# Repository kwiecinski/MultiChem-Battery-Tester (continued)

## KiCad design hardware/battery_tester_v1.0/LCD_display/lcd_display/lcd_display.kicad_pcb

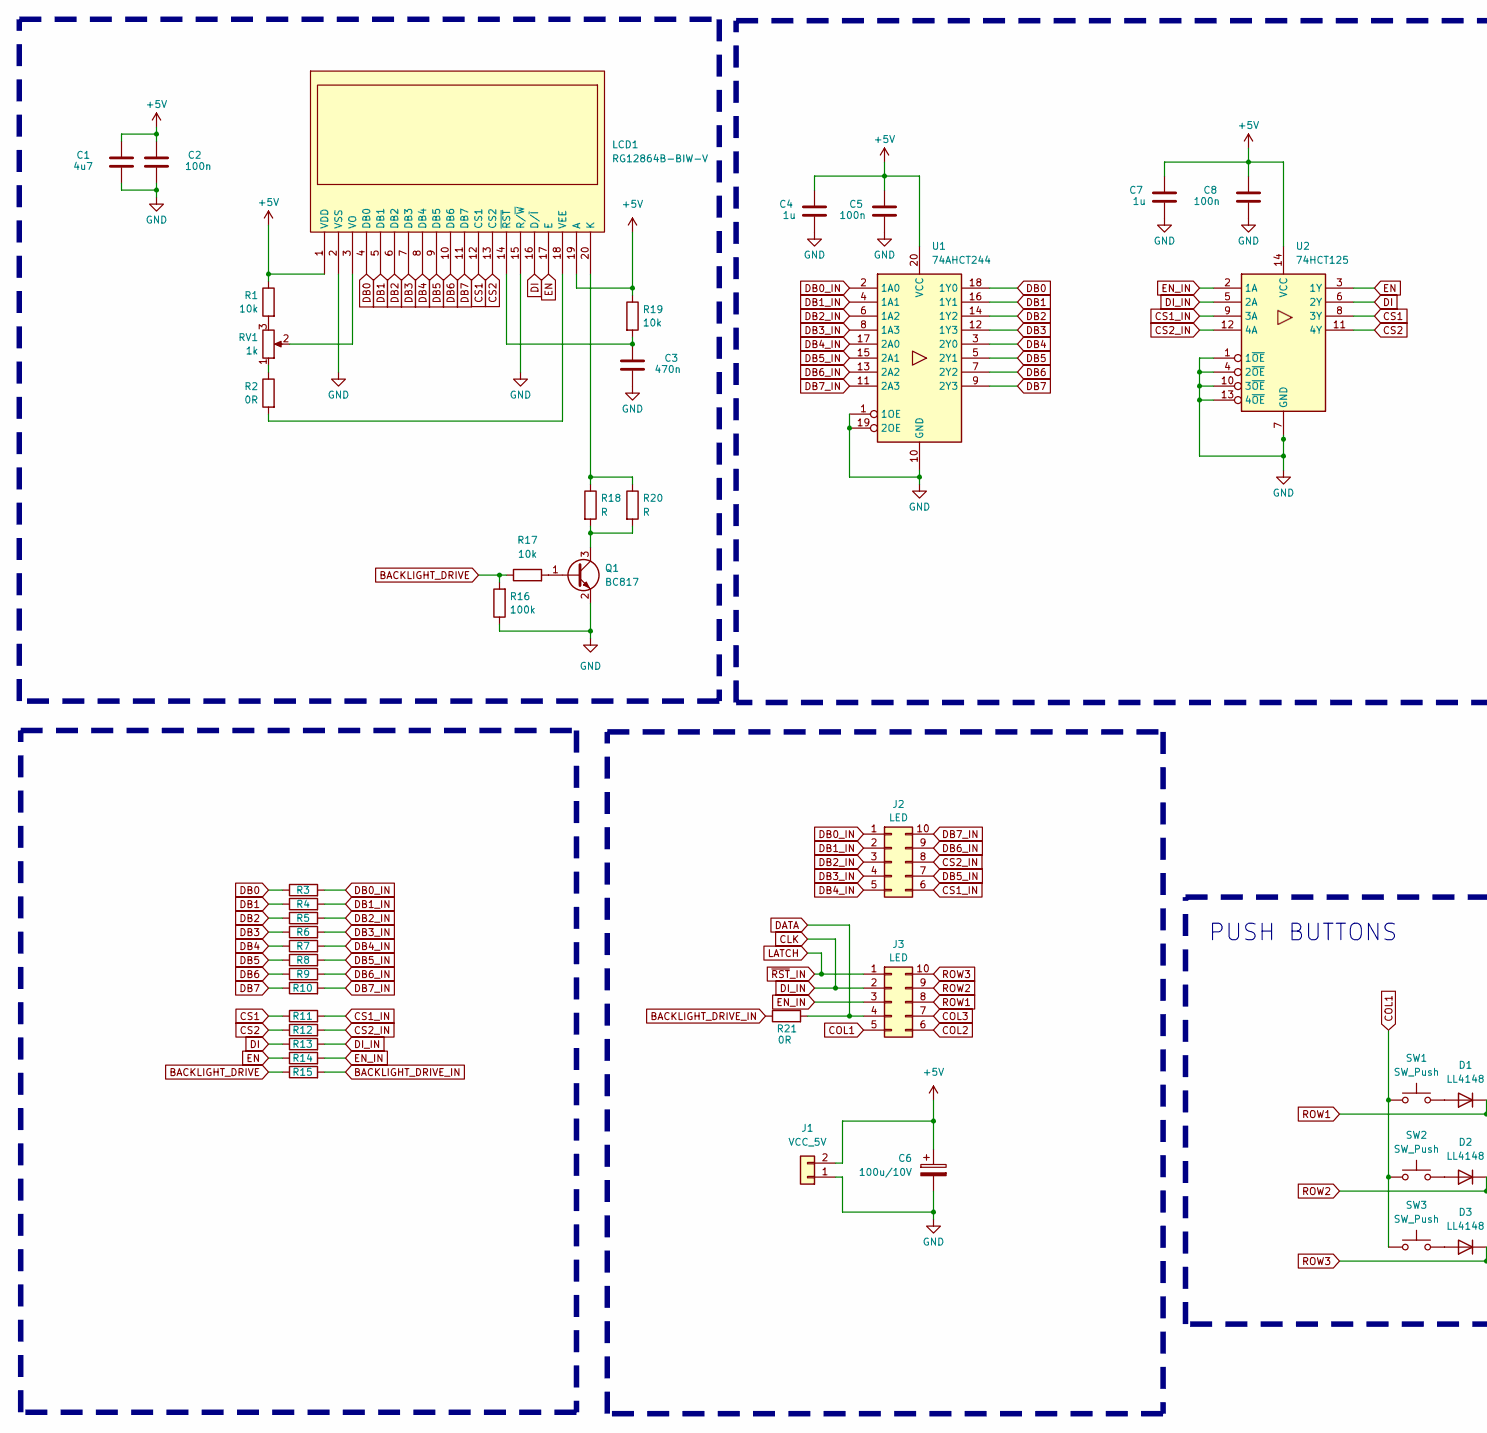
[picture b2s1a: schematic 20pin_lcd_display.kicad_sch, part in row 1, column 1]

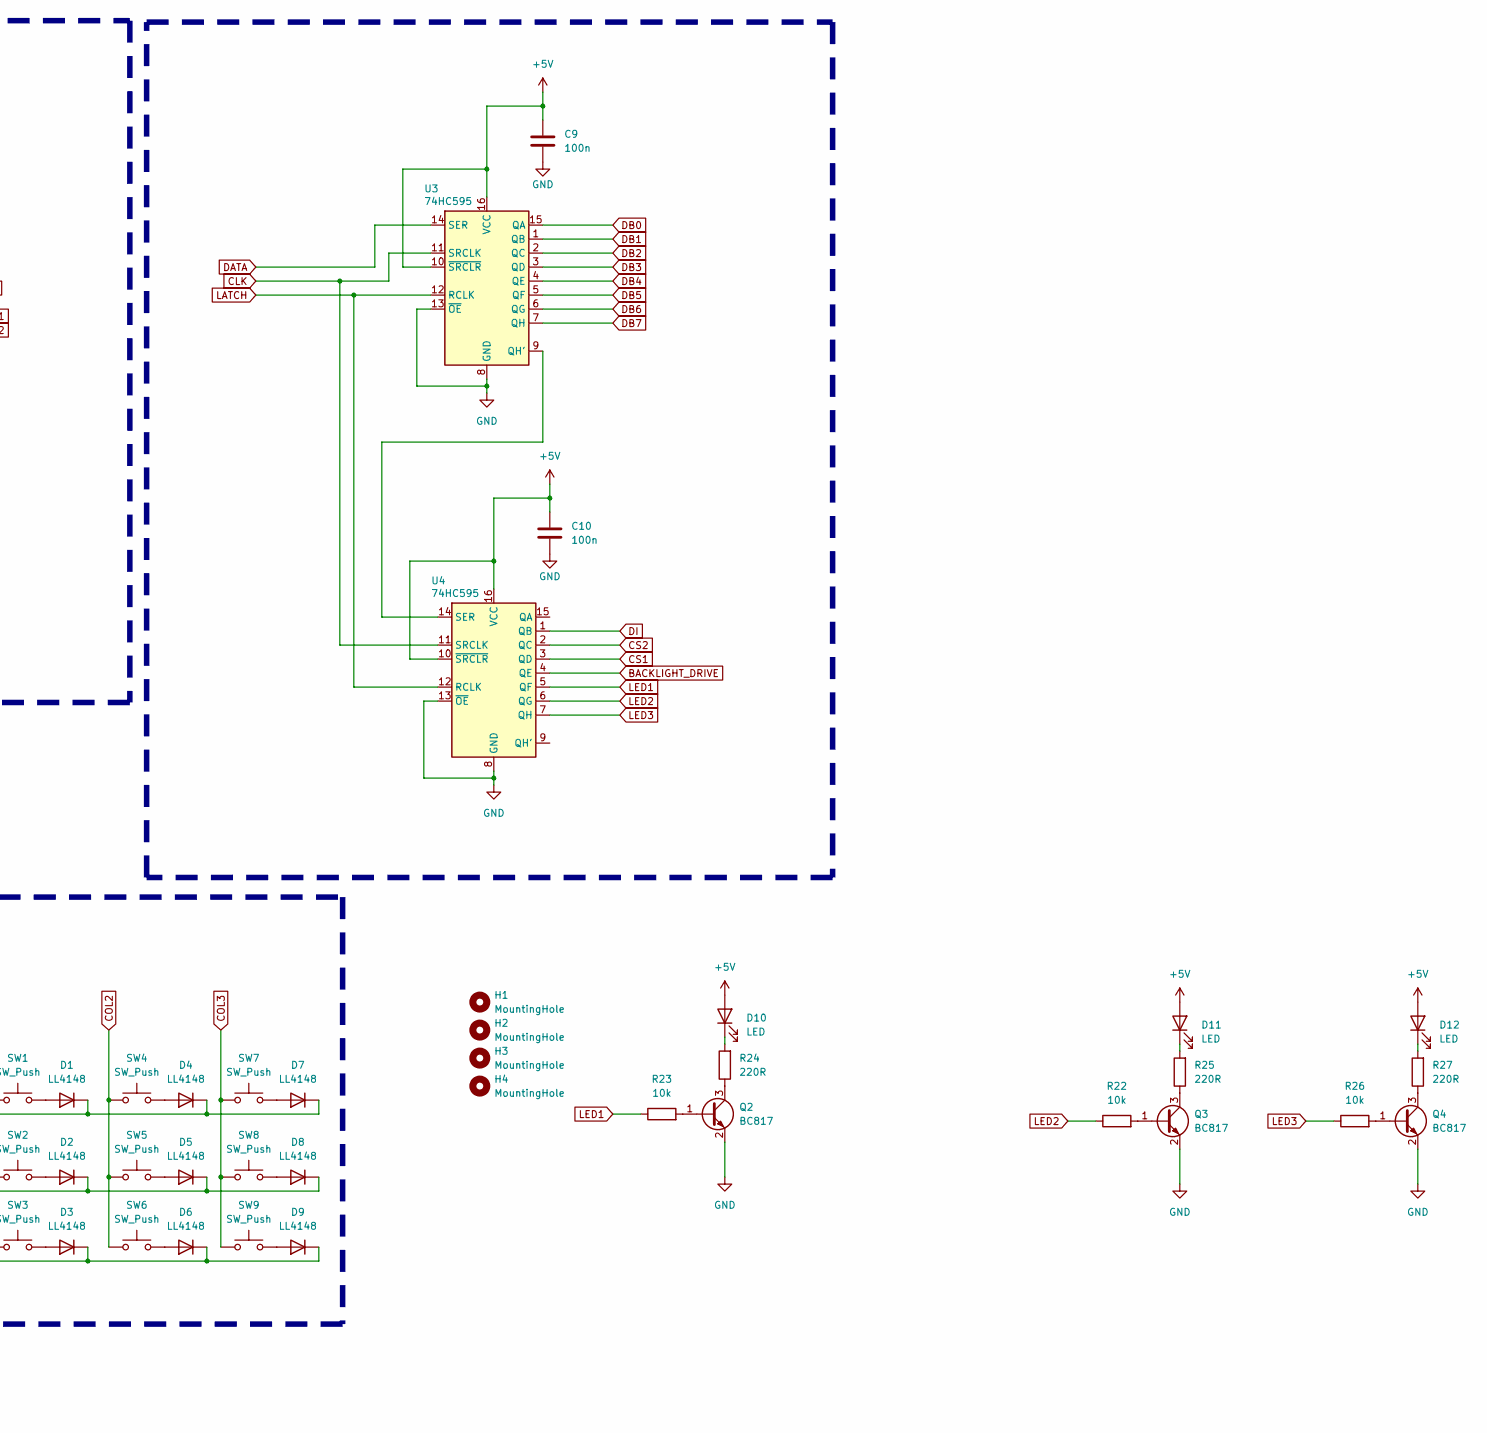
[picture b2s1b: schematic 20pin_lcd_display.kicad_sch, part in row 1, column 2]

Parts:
C1: 4u7; C_0805_2012Metric_Pad1.18x1.45mm_HandSolder
C2, C5, C8: 100n; C_0805_2012Metric_Pad1.18x1.45mm_HandSolder
C3: 470n; C_0805_2012Metric_Pad1.18x1.45mm_HandSolder
C4, C7: 1u; C_0805_2012Metric_Pad1.18x1.45mm_HandSolder
C6: 100u/10V; CP_Radial_D8.0mm_P3.80mm
C9, C10: 100n; C_0805_2012Metric
D1, D2, D3, D4, D5, D6, D7, D8, D9: LL4148; D_MiniMELF
D10, D11, D12: LED; LED_D5.0mm
H1, H2, H3, H4: MountingHole; Mount-Hole-3mm
J1: VCC_5V; JST_XA_B02B-XASK-1_1x02_P2.50mm_Vertical
J2, J3: LED; IDC-Header_2x05_P2.54mm_Vertical
LCD1: RG12864B-BIW-V; RG12864B_FULL
Q1, Q2, Q3, Q4: BC817; SOT-23
R1, R17, R19, R22, R23, R26: 10k; R_0805_2012Metric_Pad1.20x1.40mm_HandSolder
R2, R3, R4, R5, R6, R7, R8, R9, R10, R11, R12, R13, R14, R15, R21: 0R; R_0805_2012Metric_Pad1.20x1.40mm_HandSolder
R16: 100k; R_0805_2012Metric_Pad1.20x1.40mm_HandSolder
R18, R20: R; R_1206_3216Metric
R24, R25, R27: 220R; R_0805_2012Metric_Pad1.20x1.40mm_HandSolder
RV1: 1k; Potentiometer_ACP_CA9-V10_Vertical_Hole
SW1, SW2, SW3, SW4, SW5, SW6, SW7, SW8, SW9: SW_Push; SW_PUSH_6mm
U1: 74AHCT244; SOIC-20W_7.5x12.8mm_P1.27mm
U2: 74HCT125; SO-14_3.9x8.65mm_P1.27mm
U3, U4: 74HC595; SOIC-16_3.9x9.9mm_P1.27mm

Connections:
+5V: C1.1, C2.1, C4.1, C5.1, C6.1, C7.1, C8.1, C9.1, C10.1, D10.2 (A), D11.2 (A), D12.2 (A), J1.2, LCD1.1 (VDD), LCD1.19 (A), R1.1, R19.1, U1.20 (VCC), U2.14 (VCC), U3.10 (~SRCLR), U3.16 (VCC), U4.10 (~SRCLR), U4.16 (VCC)
BACKLIGHT_DRIVE: R15.1, R16.2, R17.1, U4.4 (QE)
BACKLIGHT_DRIVE_IN: R15.2, R21.1
CLK: J3.2, R13.2, U2.5 (2A), U3.11 (SRCLK), U4.11 (SRCLK)
COL1: J3.5, SW1.1, SW2.1, SW3.1
COL2: J3.6, SW4.1, SW5.1, SW6.1
COL3: J3.7, SW7.1, SW8.1, SW9.1
CS1: LCD1.12 (CS1), R11.1, U2.8 (3Y), U4.3 (QD)
CS1_IN: J2.6, R11.2, U2.9 (3A)
CS2: LCD1.13 (CS2), R12.1, U2.11 (4Y), U4.2 (QC)
CS2_IN: J2.8, R12.2, U2.12 (4A)
DATA: J3.4, R21.2, U3.14 (SER)
DB0: LCD1.4 (DB0), R3.1, U1.18 (1Y0), U3.15 (QA)
DB0_IN: J2.1, R3.2, U1.2 (1A0)
DB1: LCD1.5 (DB1), R4.1, U1.16 (1Y1), U3.1 (QB)
DB1_IN: J2.2, R4.2, U1.4 (1A1)
DB2: LCD1.6 (DB2), R5.1, U1.14 (1Y2), U3.2 (QC)
DB2_IN: J2.3, R5.2, U1.6 (1A2)
DB3: LCD1.7 (DB3), R6.1, U1.12 (1Y3), U3.3 (QD)
DB3_IN: J2.4, R6.2, U1.8 (1A3)
DB4: LCD1.8 (DB4), R7.1, U1.3 (2Y0), U3.4 (QE)
DB4_IN: J2.5, R7.2, U1.17 (2A0)
DB5: LCD1.9 (DB5), R8.1, U1.5 (2Y1), U3.5 (QF)
DB5_IN: J2.7, R8.2, U1.15 (2A1)
DB6: LCD1.10 (DB6), R9.1, U1.7 (2Y2), U3.6 (QG)
DB6_IN: J2.9, R9.2, U1.13 (2A2)
DB7: LCD1.11 (DB7), R10.1, U1.9 (2Y3), U3.7 (QH)
DB7_IN: J2.10, R10.2, U1.11 (2A3)
DI: LCD1.16 (D/~I), R13.1, U2.6 (2Y), U4.1 (QB)
EN: LCD1.17 (E), R14.1, U2.3 (1Y)
EN_IN: J3.3, R14.2, U2.2 (1A)
GND: C1.2, C2.2, C3.2, C4.2, C5.2, C6.2, C7.2, C8.2, C9.2, C10.2, J1.1, LCD1.2 (VSS), LCD1.15 (R/~W), Q1.2 (E), Q2.2 (E), Q3.2 (E), Q4.2 (E), R16.1, U1.1 (1OE), U1.10 (GND), U1.19 (2OE), U2.1 (1~OE), U2.4 (2~OE), U2.7 (GND), U2.10 (3~OE), U2.13 (4~OE), U3.8 (GND), U3.13 (~OE), U4.8 (GND), U4.13 (~OE)
LATCH: J3.1, U3.12 (RCLK), U4.12 (RCLK)
LED1: R23.1, U4.5 (QF)
LED2: R22.1, U4.6 (QG)
LED3: R26.1, U4.7 (QH)
unnamed: D1.2 (A), SW1.2
unnamed: D2.2 (A), SW2.2
unnamed: D3.2 (A), SW3.2
unnamed: D4.2 (A), SW4.2
unnamed: D5.2 (A), SW5.2
unnamed: D6.2 (A), SW6.2
unnamed: D7.2 (A), SW7.2
unnamed: D8.2 (A), SW8.2
unnamed: D9.2 (A), SW9.2
unnamed: D10.1 (K), R24.2
unnamed: D11.1 (K), R25.2
unnamed: D12.1 (K), R27.2
unnamed: LCD1.20 (K), R18.1, R20.1
unnamed: LCD1.18 (VEE), R2.2
unnamed: LCD1.3 (VO), RV1.2
unnamed: C3.1, LCD1.14 (~RST), R19.2
unnamed: Q1.1 (B), R17.2
unnamed: Q1.3 (C), R18.2, R20.2
unnamed: Q2.1 (B), R23.2
unnamed: Q2.3 (C), R24.1
unnamed: Q3.1 (B), R22.2
unnamed: Q3.3 (C), R25.1
unnamed: Q4.1 (B), R26.2
unnamed: Q4.3 (C), R27.1
unnamed: R1.2, RV1.3
unnamed: R2.1, RV1.1
unnamed: U3.9 (QH'), U4.14 (SER)
ROW1: D1.1 (K), D4.1 (K), D7.1 (K), J3.8
ROW2: D2.1 (K), D5.1 (K), D8.1 (K), J3.9
ROW3: D3.1 (K), D6.1 (K), D9.1 (K), J3.10

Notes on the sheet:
PUSH BUTTONS

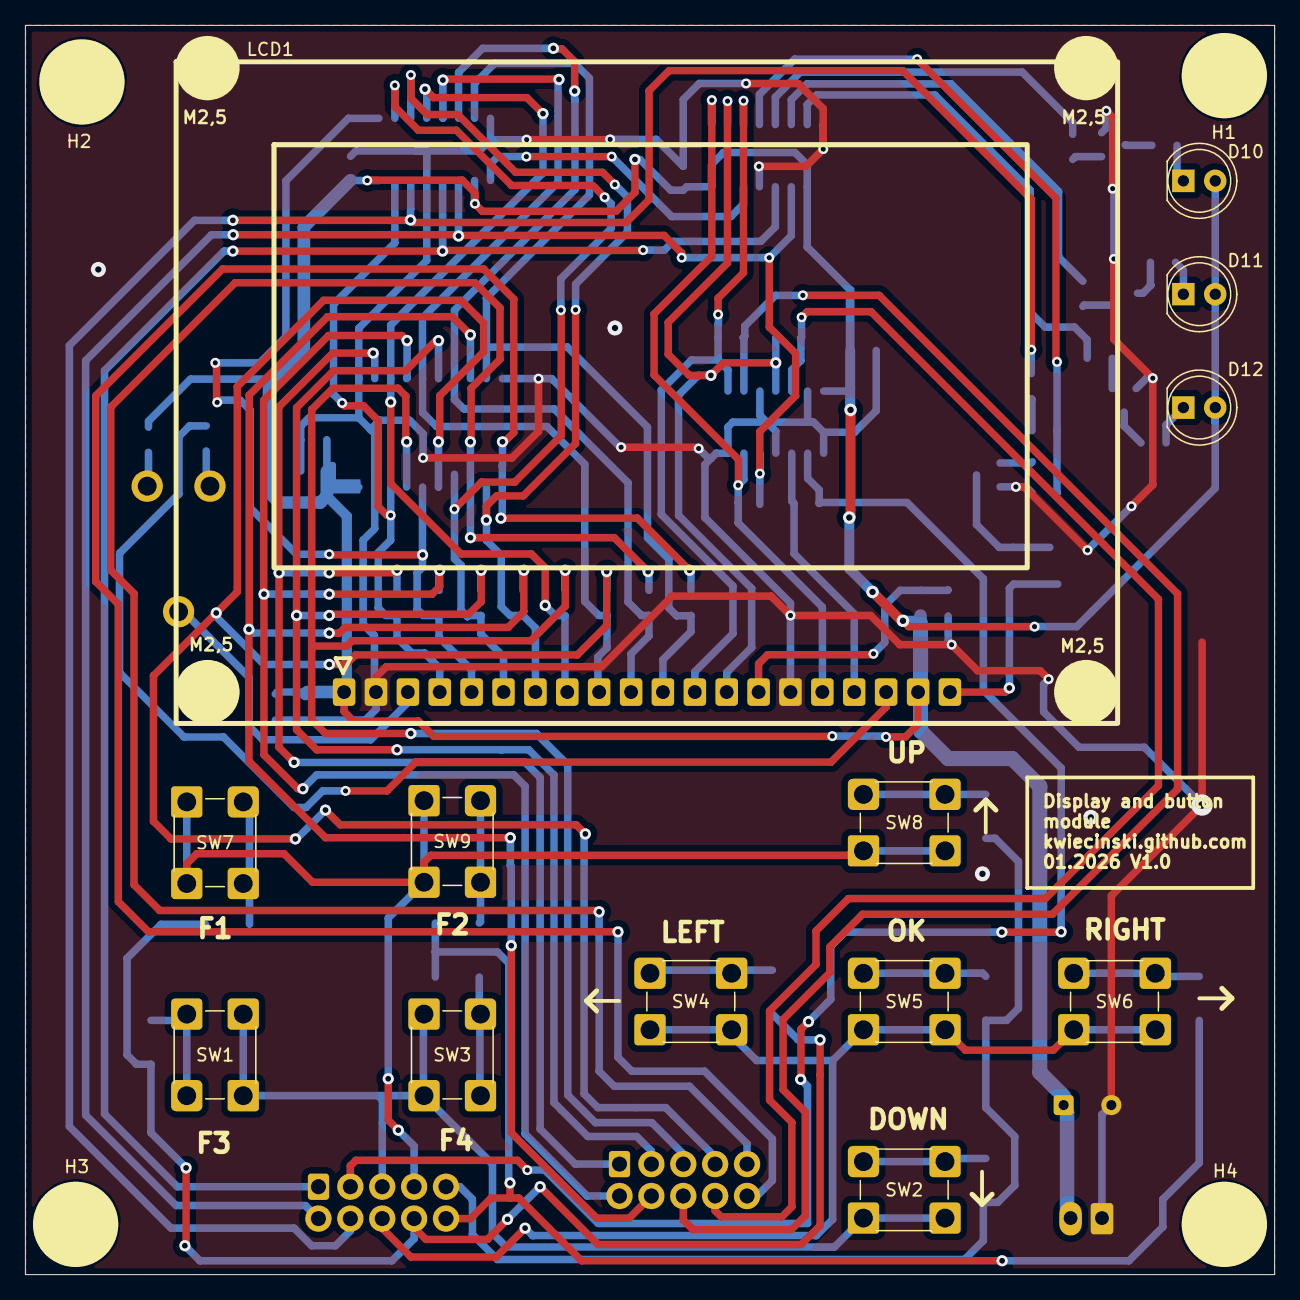
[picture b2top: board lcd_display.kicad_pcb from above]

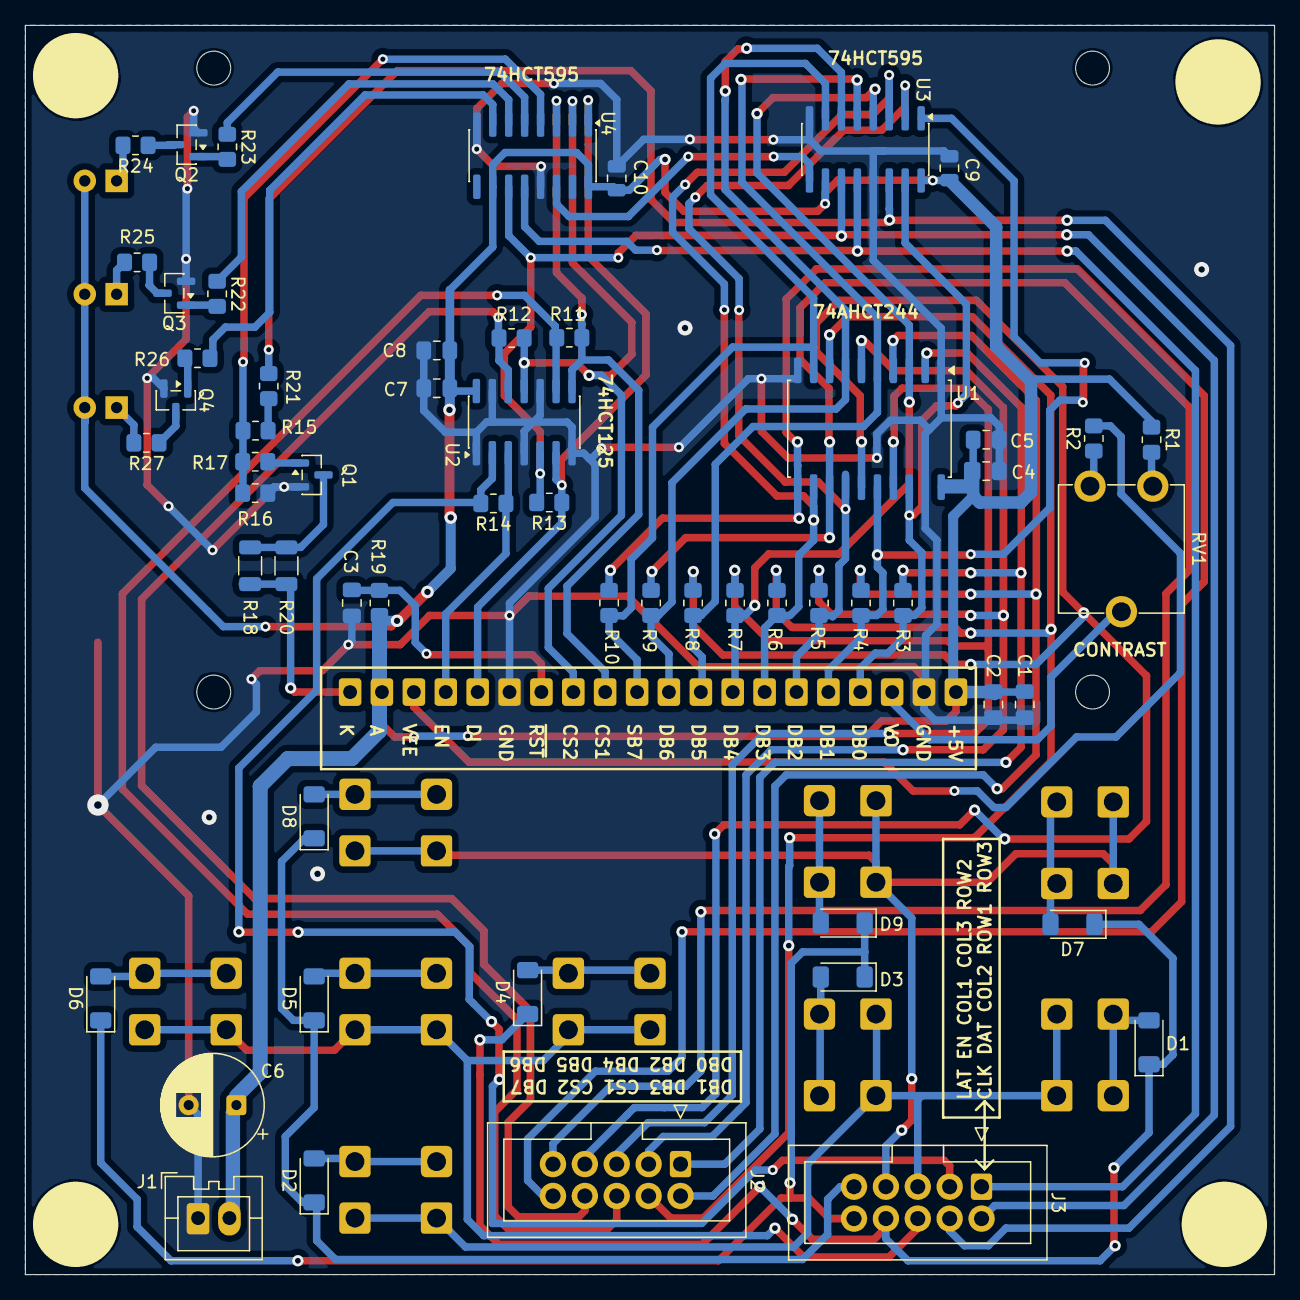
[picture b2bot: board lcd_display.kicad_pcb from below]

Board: 2 copper layers, 99.5 x 99.5 mm, 75 parts (58 on the bottom side), 66 nets.

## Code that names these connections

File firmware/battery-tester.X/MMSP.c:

#include <xc.h>
#include <stdio.h>
#include "peripherials/UART.h"
#include "main.h"


void setSPI_Interface(void) 
{
    // SPI1 module
    TRISCbits.RC3 = 0;    //SST25_CLK
    TRISCbits.RC4 = 1;    //SST25_DI
    TRISCbits.RC5 = 0;    //SST25_DO
    TRISFbits.RF7 = 0;    //SST25_CS
    
    SSP1CON1bits.SSPEN = 1;
    SSP1CON1bits.SSPM1=1;
    //Mode 3 SPI
    SSP1CON1bits.CKP = 1; //1 = Idle state for clock is a high level
    SSP1STATbits.CKE = 0; //0 = Transmit occurs on transition from Idle to active clock state
    
}
uint8_t SPI_Exchange(uint8_t data) 
{
    SSP1BUF = data;              // Load data into the buffer
    while (!SSP1STATbits.BF);    // Wait for the transfer to complete
    return SSP1BUF;              // Return received data
}

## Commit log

2024-01-09 Add code and docs
2024-01-12 set up timer0, fix problem with compiling button library
2024-01-19 Buttons now working
2024-01-24 add menu batt values functions
2024-01-25 creation of menu concept
2024-01-26 Menu progress
2024-01-30 menu cleanup, add option menu 1
2024-02-06 Add settings1 menu
2024-02-07 Add settings2 menu
2024-02-08 Navigation between menu
2024-02-15 add menu settings 4 and 5
2024-02-16 settings parameters edit functions
2024-02-20 working on parameters menu
2024-02-21 making editable parameters for settings 1&2 menu
2024-02-21 Update Linguist overrides
2024-02-22 settings 3 menu
2024-02-23 Add settings 4 parameters menu
2024-02-26 add settings 5 parameters edition
2024-02-29 Menu done, but as always some minor or major bugs still exits
2024-03-06 Initializing I2C, add memory map
2024-03-08 success initialization of SST25V040 flash memory
2024-03-11 Creation of memory mam, first functions of wear leveling algorithm
2024-03-12 Add wear leveling static buffor functions, update memory map
2024-03-13 Writing parameter data to flash, try to add aii flash function
2024-03-14 add auto increment for flash memory, working on memory functions
2024-03-15 Introducing pointers to diffrent battery chemistry parameters
2024-03-29 add settings struct repacement
2024-04-26 memory parameters change
2024-05-10 Add memory settings write function, tests
2024-05-14 Memory data dumping and debuging
2024-05-16 Read and write settings from flash is working
2024-05-20 memory organisation progress
2024-05-21 add wear leveling functions for mesaurment data, beautyfy memory tab
2024-05-22 measurment data storage functions progress
2024-05-24 measaurment data storage function progress, fixing warnings
2024-05-28 Resolving warnings and other compilation problems
2024-05-31 add read measurements function, problem with include headers
2024-06-04 fixed heeders, write memory test function
2024-06-05 fixin saving measurement data functions
2026-01-14 create battery tester v1.0 project
2026-01-16 update schematic
2026-01-19 update battery tester
2026-01-20 update lcd pcb
2026-01-20 update lcd display + button pcb
2026-01-21 lcd pcb done
2026-01-21 update man pcb, cleanup
2026-01-22 update main pcb schematic
2026-01-23 update main pcb battery charger
2026-01-26 update charger schematic - voltage measurement
